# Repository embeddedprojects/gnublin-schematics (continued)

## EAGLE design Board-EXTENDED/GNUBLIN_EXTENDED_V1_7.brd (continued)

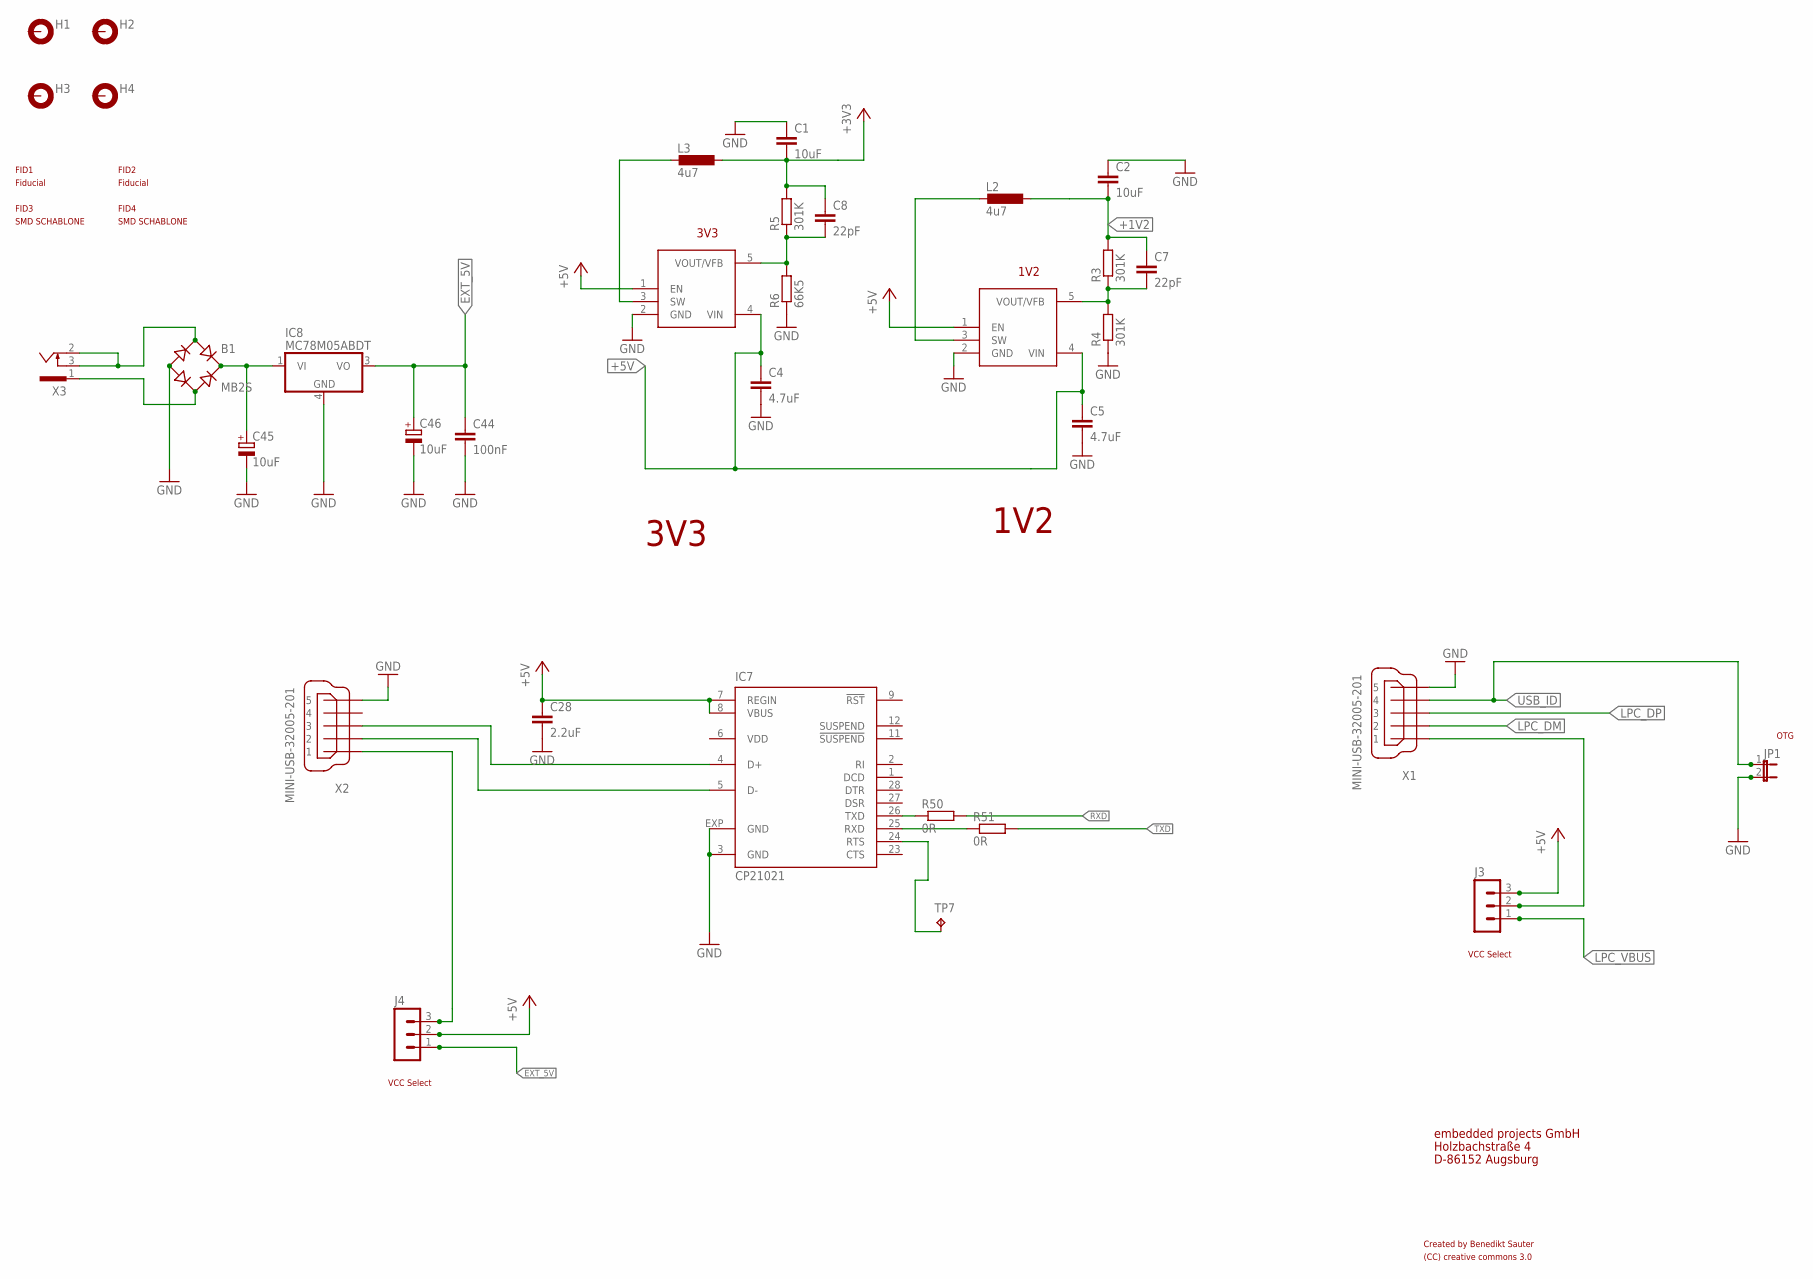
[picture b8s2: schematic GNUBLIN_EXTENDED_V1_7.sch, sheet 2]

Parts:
B1: MB2S; SOIC-4
C1, C2: 10uF; C0805
C4, C5: 4.7uF; C0805
C7, C8: 22pF; C0805
C28: 2.2uF; C0805
C44: 100nF; C0805
C45, C46: 10uF; D/7343-31R
FID1, FID2, FID3, FID4: PASSERMARKEN_FIDUCIAL
H1, H2, H3, H4: MOUNT-PAD-ROUND2.8; 2,8-PAD
IC2, IC3: AS1324; TSOT23
IC7: CP21021; MLP28
IC8: MC78M05ABDT; DPACK_3
J3, J4: MA03-1
JP1: JP1E; JP1
L2, L3: 4u7; PSU3014
R3, R4, R5: 301K; R0805
R6: 66K5; R0805
R50, R51: 0R; R0805
TP7: TPTP08R; TP08R
X1, X2: MINI-USB-32005-201; 32005-201
X3: 733980-62

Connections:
5V_USB: J4.3, X2.1
+1V2: C2.2, C7.1, L2.2, R3.2; also elsewhere on the board
+3V3: C1.2, C8.1, L3.2, R5.2; also elsewhere on the board
+5V: C4.1, C5.1, C28.1, IC2.1 (EN), IC2.4 (VIN), IC3.1 (EN), IC3.4 (VIN), IC7.7 (REGIN), IC7.8 (VBUS), J3.3, J4.2; also elsewhere on the board
EXT_5V: C44.1, C46.+, IC8.3 (VO), J4.1
GND: B1.-, C1.1, C2.1, C4.2, C5.2, C28.2, C44.2, C45.-, C46.-, IC2.2 (GND), IC3.2 (GND), IC7.3 (GND), IC7.EXP (GND), IC8.4 (GND), JP1.2, R4.1, R6.1, X1.5, X2.5; also elsewhere on the board
LPC_DM: X1.2; also elsewhere on the board
LPC_DP: X1.3; also elsewhere on the board
LPC_VBUS: J3.1; also elsewhere on the board
unnamed: IC7.26 (TXD), R50.1
unnamed: J3.2, X1.1
unnamed: IC7.4 (D+), X2.3
unnamed: IC7.5 (D-), X2.2
unnamed: IC2.3 (SW), L2.1
unnamed: IC7.25 (RXD), R51.1
unnamed: IC7.24 (RTS), TP7.TP
unnamed: C7.2, IC2.5 (VOUT/VFB), R3.1, R4.2
unnamed: B1.+, C45.+, IC8.1 (VI)
unnamed: B1.~2 (AC2), X3.1
unnamed: B1.~1 (AC1), X3.2, X3.3
unnamed: IC3.3 (SW), L3.1
unnamed: C8.2, IC3.5 (VOUT/VFB), R5.1, R6.2
RXD: R50.2; also elsewhere on the board
TXD: R51.2; also elsewhere on the board
USB_ID: JP1.1, X1.4; also elsewhere on the board
VDD: IC7.6 (VDD)

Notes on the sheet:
Created by Benedikt Sauter
3V3
1V2
embedded projects GmbH
Holzbachstraße 4
D-86152 Augsburg
VCC Select
OTG
(CC) creative commons 3.0

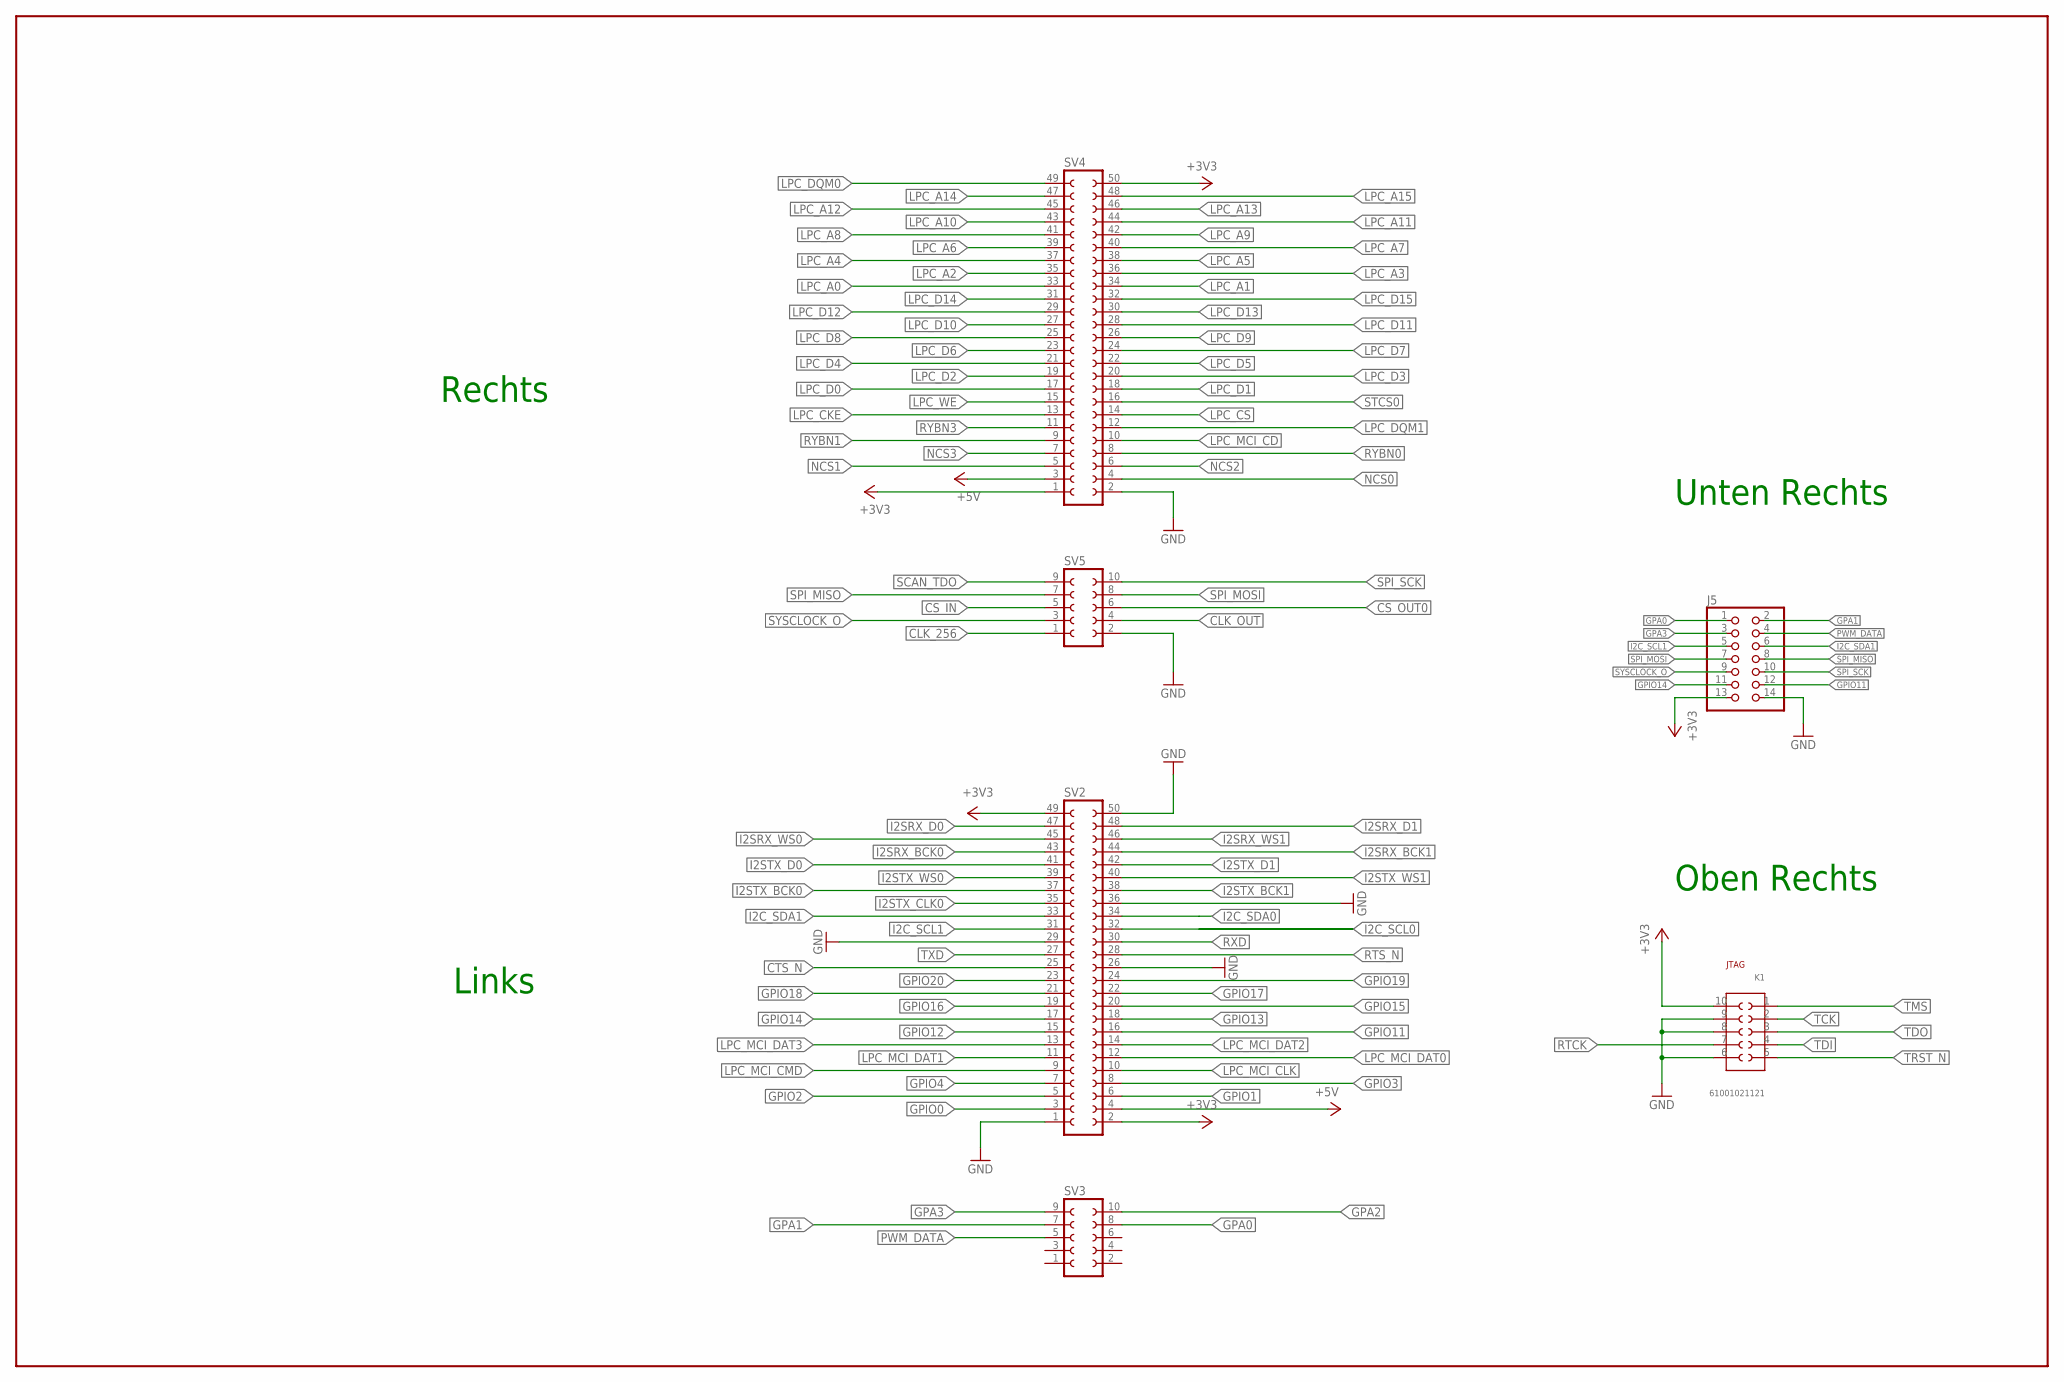
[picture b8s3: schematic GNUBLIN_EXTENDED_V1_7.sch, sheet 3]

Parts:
J5: PINHD-2X7; 2X07
K1: 61001021121
SV2, SV4: FE25-2
SV3, SV5: FE05-2

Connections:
+3V3: J5.13, K1.10, SV2.2, SV2.49, SV4.1, SV4.50; also elsewhere on the board
+5V: SV2.4, SV4.3; also elsewhere on the board
CLK_256: SV5.1; also elsewhere on the board
CLK_OUT: SV5.4; also elsewhere on the board
CS_IN: SV5.5; also elsewhere on the board
CS_OUT0: SV5.6; also elsewhere on the board
CTS_N: SV2.25; also elsewhere on the board
GND: J5.14, K1.6, K1.8, K1.9, SV2.1, SV2.26, SV2.29, SV2.36, SV2.50, SV4.2, SV5.2; also elsewhere on the board
GPA0: J5.1, SV3.8; also elsewhere on the board
GPA1: J5.2, SV3.7; also elsewhere on the board
GPA2: SV3.10; also elsewhere on the board
GPA3: J5.3, SV3.9; also elsewhere on the board
GPIO0: SV2.3; also elsewhere on the board
GPIO1: SV2.6; also elsewhere on the board
GPIO2: SV2.5; also elsewhere on the board
GPIO3: SV2.8; also elsewhere on the board
GPIO4: SV2.7; also elsewhere on the board
GPIO11: J5.12, SV2.16; also elsewhere on the board
GPIO12: SV2.15; also elsewhere on the board
GPIO13: SV2.18; also elsewhere on the board
GPIO14: J5.11, SV2.17; also elsewhere on the board
GPIO15: SV2.20; also elsewhere on the board
GPIO16: SV2.19; also elsewhere on the board
GPIO17: SV2.22; also elsewhere on the board
GPIO18: SV2.21; also elsewhere on the board
GPIO19: SV2.24; also elsewhere on the board
GPIO20: SV2.23; also elsewhere on the board
I2C_SCL0: SV2.32; also elsewhere on the board
I2C_SCL1: J5.5, SV2.31; also elsewhere on the board
I2C_SDA0: SV2.34; also elsewhere on the board
I2C_SDA1: J5.6, SV2.33; also elsewhere on the board
I2SRX_BCK0: SV2.43; also elsewhere on the board
I2SRX_BCK1: SV2.44; also elsewhere on the board
I2SRX_D0: SV2.47; also elsewhere on the board
I2SRX_D1: SV2.48; also elsewhere on the board
I2SRX_WS0: SV2.45; also elsewhere on the board
I2SRX_WS1: SV2.46; also elsewhere on the board
I2STX_BCK0: SV2.37; also elsewhere on the board
I2STX_BCK1: SV2.38; also elsewhere on the board
I2STX_CLK0: SV2.35; also elsewhere on the board
I2STX_D0: SV2.41; also elsewhere on the board
I2STX_D1: SV2.42; also elsewhere on the board
I2STX_WS0: SV2.39; also elsewhere on the board
I2STX_WS1: SV2.40; also elsewhere on the board
LPC_A0: SV4.33; also elsewhere on the board
LPC_A1: SV4.34; also elsewhere on the board
LPC_A2: SV4.35; also elsewhere on the board
LPC_A3: SV4.36; also elsewhere on the board
LPC_A4: SV4.37; also elsewhere on the board
LPC_A5: SV4.38; also elsewhere on the board
LPC_A6: SV4.39; also elsewhere on the board
LPC_A7: SV4.40; also elsewhere on the board
LPC_A8: SV4.41; also elsewhere on the board
LPC_A9: SV4.42; also elsewhere on the board
LPC_A10: SV4.43; also elsewhere on the board
LPC_A11: SV4.44; also elsewhere on the board
LPC_A12: SV4.45; also elsewhere on the board
LPC_A13: SV4.46; also elsewhere on the board
LPC_A14: SV4.47; also elsewhere on the board
LPC_A15: SV4.48; also elsewhere on the board
LPC_CKE: SV4.13; also elsewhere on the board
LPC_CS: SV4.14; also elsewhere on the board
LPC_D0: SV4.17; also elsewhere on the board
LPC_D1: SV4.18; also elsewhere on the board
LPC_D2: SV4.19; also elsewhere on the board
LPC_D3: SV4.20; also elsewhere on the board
LPC_D4: SV4.21; also elsewhere on the board
LPC_D5: SV4.22; also elsewhere on the board
LPC_D6: SV4.23; also elsewhere on the board
LPC_D7: SV4.24; also elsewhere on the board
LPC_D8: SV4.25; also elsewhere on the board
LPC_D9: SV4.26; also elsewhere on the board
LPC_D10: SV4.27; also elsewhere on the board
LPC_D11: SV4.28; also elsewhere on the board
LPC_D12: SV4.29; also elsewhere on the board
LPC_D13: SV4.30; also elsewhere on the board
LPC_D14: SV4.31; also elsewhere on the board
LPC_D15: SV4.32; also elsewhere on the board
LPC_DQM0: SV4.49; also elsewhere on the board
LPC_DQM1: SV4.12; also elsewhere on the board
LPC_MCI_CD: SV4.10; also elsewhere on the board
LPC_MCI_CLK: SV2.10; also elsewhere on the board
LPC_MCI_CMD: SV2.9; also elsewhere on the board
LPC_MCI_DAT0: SV2.12; also elsewhere on the board
LPC_MCI_DAT1: SV2.11; also elsewhere on the board
LPC_MCI_DAT2: SV2.14; also elsewhere on the board
LPC_MCI_DAT3: SV2.13; also elsewhere on the board
LPC_WE: SV4.15; also elsewhere on the board
NCS0: SV4.4; also elsewhere on the board
NCS1: SV4.5; also elsewhere on the board
NCS2: SV4.6; also elsewhere on the board
NCS3: SV4.7; also elsewhere on the board
PWM_DATA: J5.4, SV3.5; also elsewhere on the board
RTCK: K1.7
RTS_N: SV2.28; also elsewhere on the board
RXD: SV2.30; also elsewhere on the board
RYBN0: SV4.8; also elsewhere on the board
RYBN1: SV4.9; also elsewhere on the board
RYBN3: SV4.11; also elsewhere on the board
SCAN_TDO: SV5.9; also elsewhere on the board
SPI_MISO: J5.8, SV5.7; also elsewhere on the board
SPI_MOSI: J5.7, SV5.8; also elsewhere on the board
SPI_SCK: J5.10, SV5.10; also elsewhere on the board
STCS0: SV4.16; also elsewhere on the board
SYSCLOCK_O: J5.9, SV5.3; also elsewhere on the board
TCK: K1.2; also elsewhere on the board
TDI: K1.4; also elsewhere on the board
TDO: K1.3; also elsewhere on the board
TMS: K1.1; also elsewhere on the board
TRST_N: K1.5; also elsewhere on the board
TXD: SV2.27; also elsewhere on the board

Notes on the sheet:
Links
Rechts
Unten Rechts
Oben Rechts
JTAG

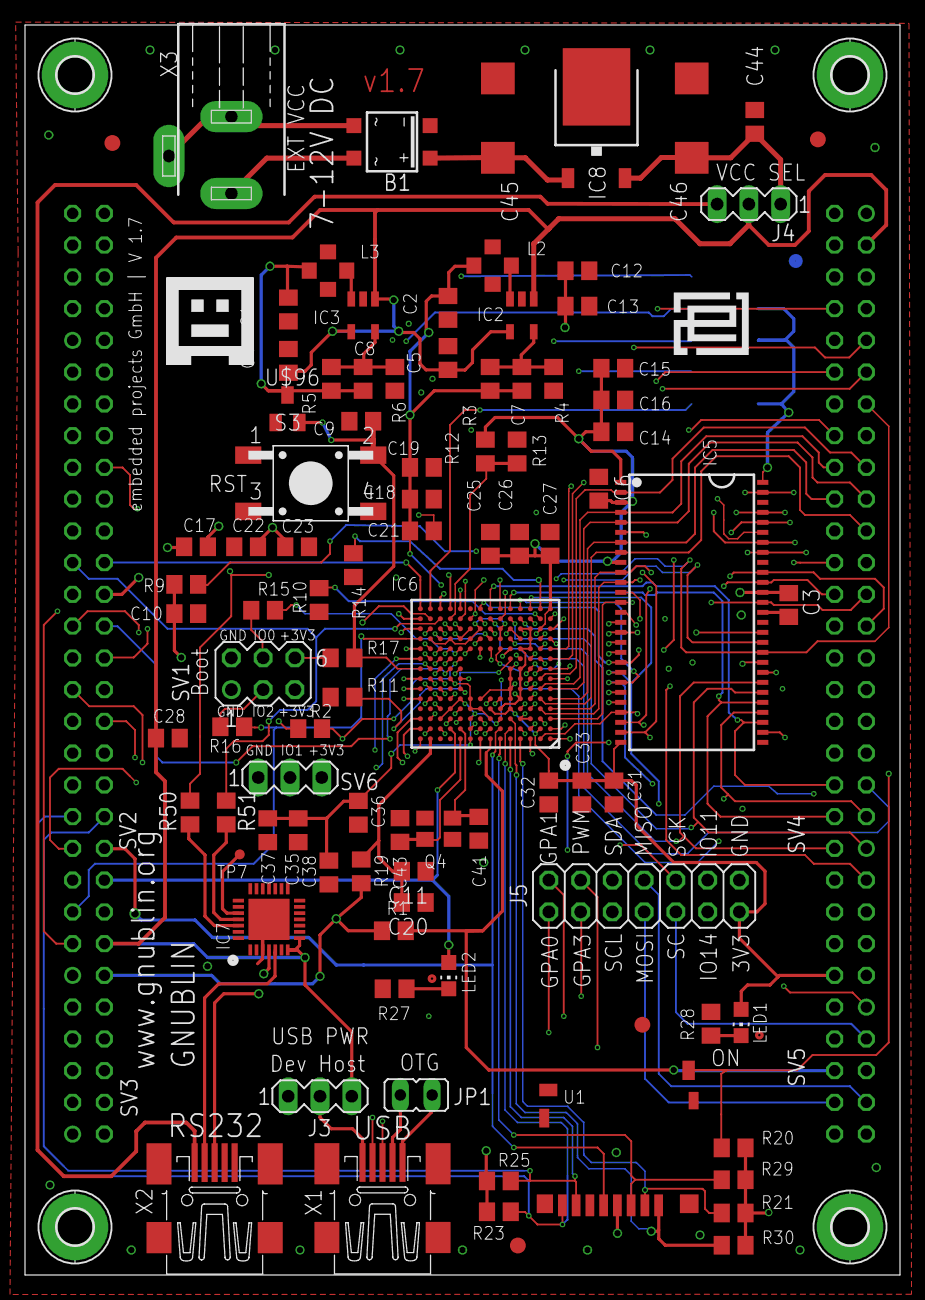
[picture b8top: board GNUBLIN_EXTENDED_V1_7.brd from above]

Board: 6 copper layers, 70.0 x 100.0 mm, 105 parts (1 on the bottom side), 145 nets.

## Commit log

2013-04-24 added MODUL_RASP-PI_BRIDGE_V100
2013-04-24 remove work files from MODUL_RASP-PI_BRIDGE_V100
2013-05-04 add many boards
2013-05-15 Boards
2013-05-15 added pdf files
2013-06-11 add Module RAIL INPUT 24V
2013-06-11 add Board-DEFAULT files
2013-06-11 add Board-DIP
2013-06-11 add files
2013-06-13 add Bridge, Extension, LCD
2013-08-23 add GnuBo
2014-03-18 add schematic RS232
2014-04-08 Add DIN-Rail In
2014-04-14 GNUBLIN DIP EASY
